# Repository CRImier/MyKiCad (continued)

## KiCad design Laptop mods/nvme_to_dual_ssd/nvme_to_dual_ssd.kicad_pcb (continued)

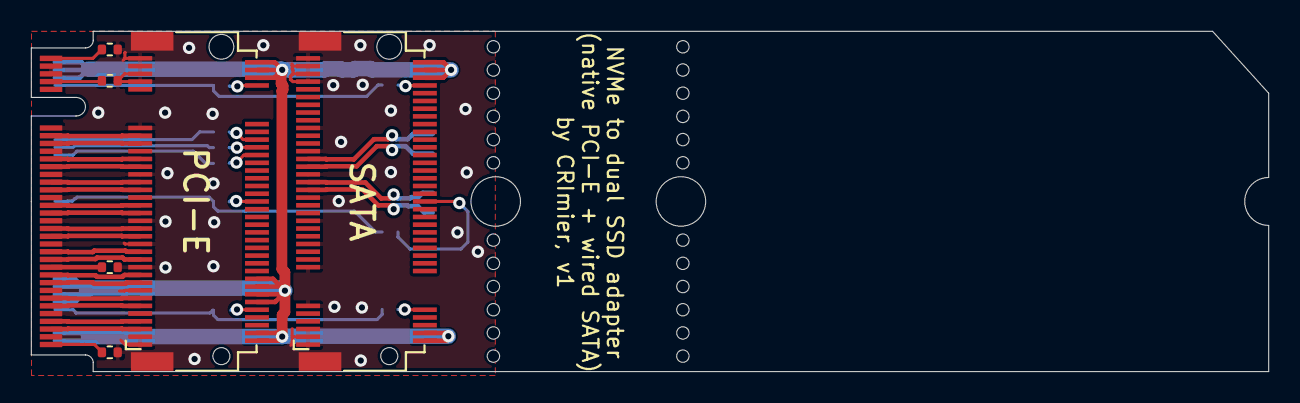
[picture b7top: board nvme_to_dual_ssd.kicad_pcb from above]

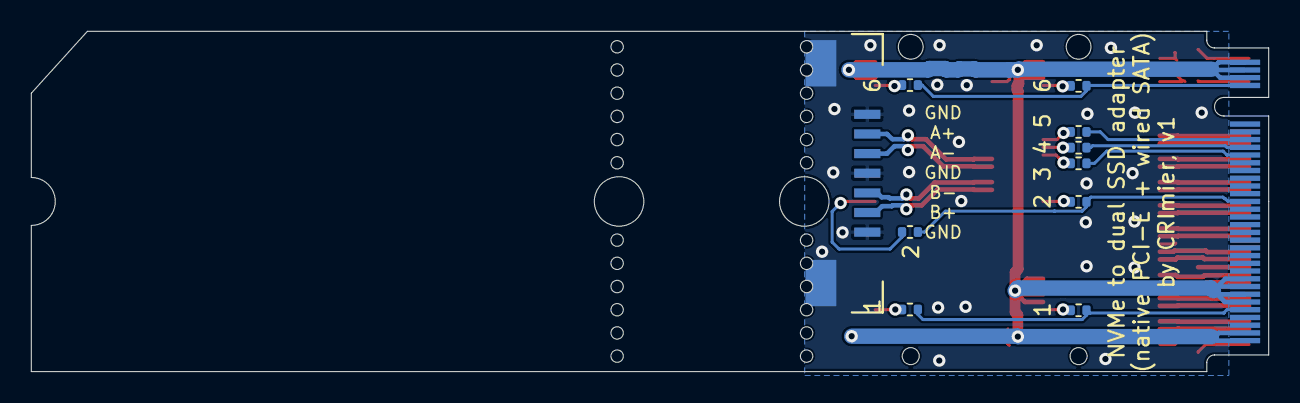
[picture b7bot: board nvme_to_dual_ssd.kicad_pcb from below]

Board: 2 copper layers, 80.0 x 22.0 mm, 17 parts (10 on the bottom side), 43 nets.
